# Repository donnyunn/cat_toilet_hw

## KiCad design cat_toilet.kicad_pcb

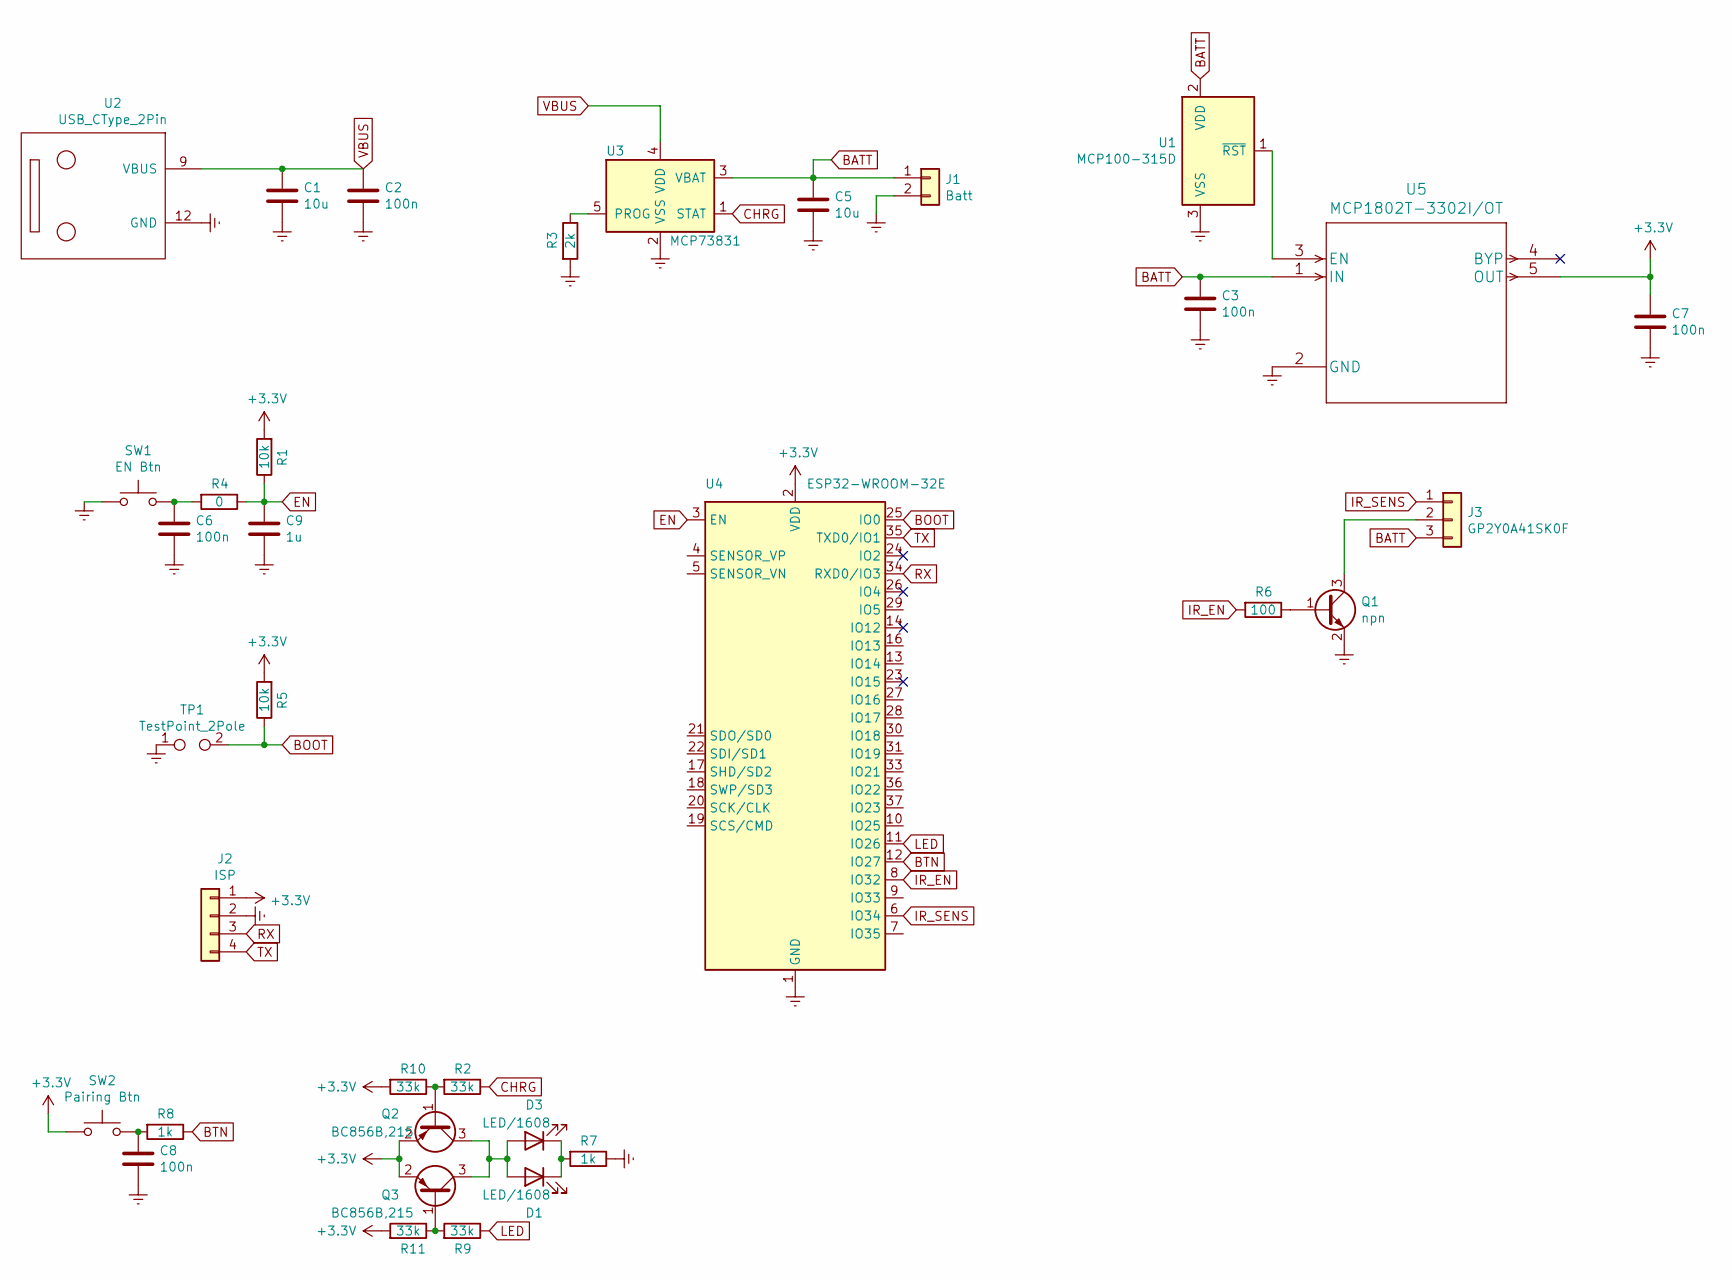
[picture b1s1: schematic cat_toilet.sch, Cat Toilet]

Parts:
C1, C5: 10u; C_0603_1608Metric; MPN 302010103
C2, C3, C6, C7, C8: 100n; C_0603_1608Metric; MPN 302010138
C9: 1u; C_0603_1608Metric; MPN 302010139
D1, D3: LED/1608; LED_0603_1608Metric; MPN SMLEN3WBC8W1
J1: Batt; boot
J2: ISP; PinHeader_1x04_P2.00mm_Vertical
J3: GP2Y0A41SK0F; JST_PH_B3B-PH-K_1x03_P2.00mm_Vertical
Q1: npn; SOT-23; MPN BC846A,215
Q2, Q3: BC856B,215; SOT-23; MPN BC856B,215
R1: 10k; R_0603_1608Metric; MPN 301010293
R2, R9, R10, R11: 33k; R_0603_1608Metric; MPN CR0603JA0333G
R3: 2k; R_0603_1608Metric; MPN 301010113
R4: 0; R_0603_1608Metric; MPN 301011968
R5: 10k; R_0603_1608Metric_Pad0.98x0.95mm_HandSolder; MPN 301010293
R6: 100; R_0603_1608Metric; MPN 301011976
R7, R8: 1k; R_0603_1608Metric; MPN 301010291
SW1: EN Btn; SW_SPST_B3U-1000P
SW2: Pairing Btn; SW_SPST_B3U-1000P; MPN B3U-1000P
TP1: TestPoint_2Pole; boot
U1: MCP100-315D; SOT-23; MPN MCP100T-315D
U2: USB_CType_2Pin; MPN USB4125-GF-A
U3: MCP73831; SOT-23-5; MPN MCP73831T-2ACI/OT
U4: ESP32-WROOM-32E; ESP32-WROOM-32; MPN ESP32-WROOM-32E(M113EH3200PH3Q0)
U5: MCP1802T-3302I/OT; SOT-23-5; MPN MCP1802T-3302I/OT

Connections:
+3V3: C7.1, J2.1, Q2.2 (E), Q3.2 (E), R1.2, R5.2, R10.2, R11.2, SW2.1, U4.2 (VDD), U5.5 (OUT)
BATT: C3.1, C5.1, J1.1, J3.3, U1.2 (VDD), U3.3 (VBAT), U5.1 (IN)
BOOT: R5.1, TP1.2, U4.25 (IO0)
BTN: R8.1, U4.12 (IO27)
CHRG: R2.1, U3.1 (STAT)
EN: C9.1, R1.1, R4.1, U4.3 (EN)
Earth: C1.2, C2.2, C3.2, C5.2, C6.2, C7.2, C8.2, C9.2, J1.2, J2.2, Q1.2 (E), R3.2, R7.1, SW1.1, TP1.1, U1.3 (VSS), U2.12 (GND), U3.2 (VSS), U4.1 (GND), U4.15 (GND), U4.38 (GND), U4.39 (GND), U5.2 (GND)
IR_EN: R6.2, U4.8 (IO32)
IR_SENS: J3.1, U4.6 (IO34)
LED: R9.1, U4.11 (IO26)
unnamed: C6.1, R4.2, SW1.2
unnamed: C8.1, R8.2, SW2.2
unnamed: D1.1 (K), D3.1 (K), R7.2
unnamed: D1.2 (A), D3.2 (A), Q2.3 (C), Q3.3 (C)
unnamed: J3.2, Q1.3 (C)
unnamed: Q1.1 (B), R6.1
unnamed: Q2.1 (B), R2.2, R10.1
unnamed: Q3.1 (B), R9.2, R11.1
unnamed: R3.1, U3.5 (PROG)
unnamed: U1.1 (~RST), U5.3 (EN)
RX: J2.3, U4.34 (RXD0/IO3)
TX: J2.4, U4.35 (TXD0/IO1)
VBUS: C1.1, C2.1, U2.9 (VBUS), U3.4 (VDD)

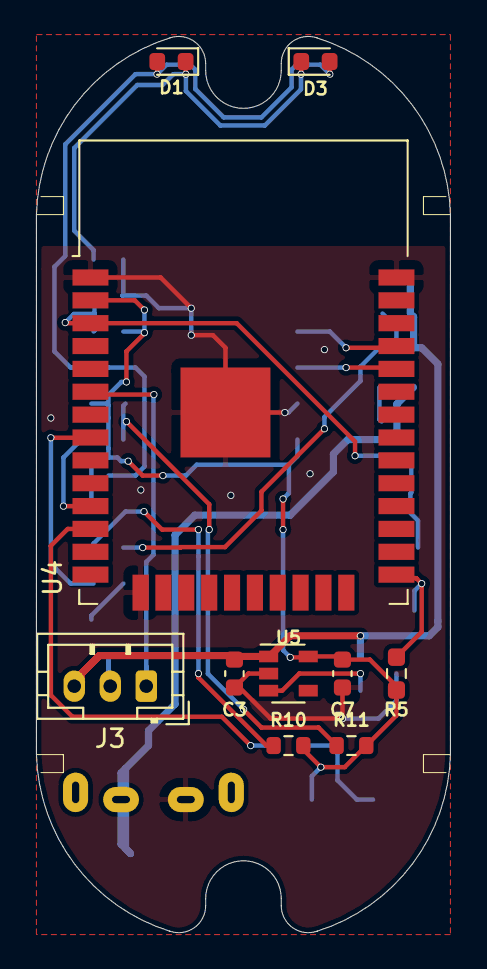
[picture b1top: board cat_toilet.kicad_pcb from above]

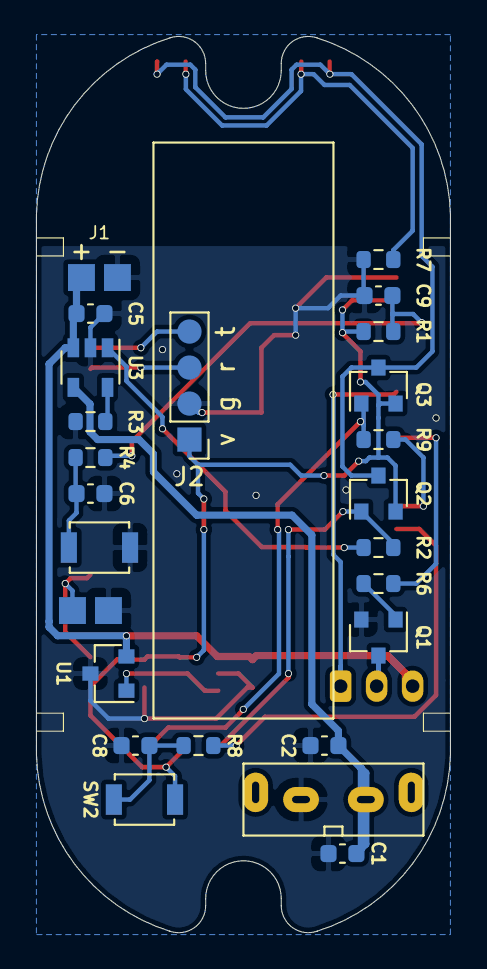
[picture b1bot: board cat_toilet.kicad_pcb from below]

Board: 2 copper layers, 23.0 x 49.8 mm, 35 parts (25 on the bottom side), 23 nets.

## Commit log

2021-08-09 2021-08-09
2021-08-12 2021-08-12
2021-08-12 2021-08-12 2
2021-08-29 2021-08-29
2021-12-14 2021-12-14
